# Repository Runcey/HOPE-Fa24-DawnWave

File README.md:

# HOPE-Fa24-DawnWave
## Install the [Espressif plugin](https://github.com/espressif/kicad-libraries) for KiCad!

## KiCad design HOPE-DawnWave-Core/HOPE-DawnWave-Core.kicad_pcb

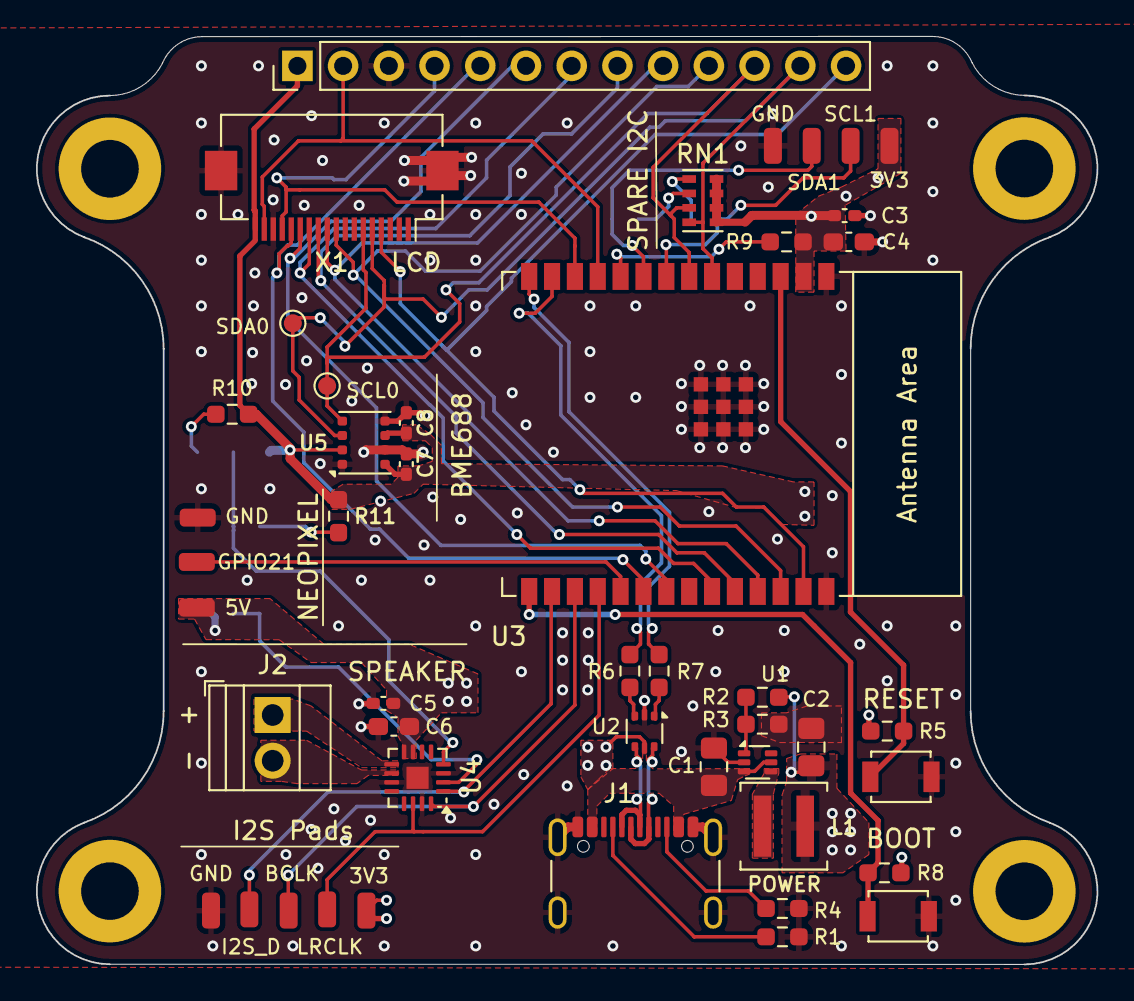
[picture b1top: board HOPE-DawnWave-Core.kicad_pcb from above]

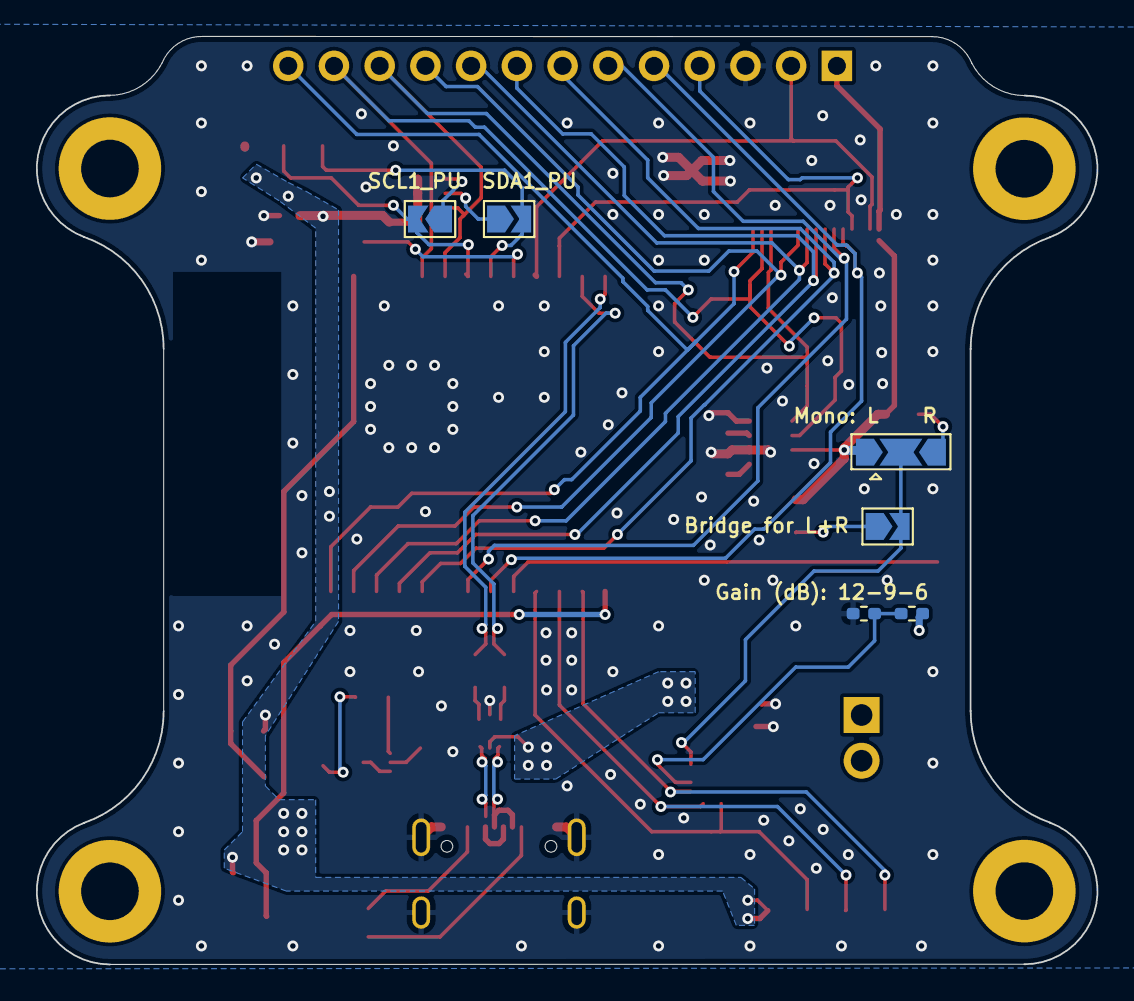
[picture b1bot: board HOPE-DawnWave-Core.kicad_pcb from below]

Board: 2 copper layers, 58.9 x 51.5 mm, 56 parts (6 on the bottom side), 41 nets.

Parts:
C1: 4.7u; C_0805_2012Metric_Pad1.18x1.45mm_HandSolder
C2: 22u; C_0805_2012Metric_Pad1.18x1.45mm_HandSolder
C3, C5: 100n; C_0402_1005Metric_Pad0.74x0.62mm_HandSolder
C4: 22u; C_0603_1608Metric_Pad1.08x0.95mm_HandSolder
C6: 10u; C_0603_1608Metric_Pad1.08x0.95mm_HandSolder
C7, C8: 0.1 µ; C_0402_1005Metric_Pad0.74x0.62mm_HandSolder
H1, H2, H3, H4: MountingHole; MountingHole_3.2mm_M3_ISO7380_Pad
J1: USB_C_Receptacle_USB2.0_16P; USB_C_Receptacle_GCT_USB4105-xx-A_16P_TopMnt_Horizontal
J2: Screw_Terminal_01x02; TerminalBlock_Xinya_XY308-2.54-2P_1x02_P2.54mm_Horizontal
J3: Conn_01x13_Pin; PinHeader_1x13_P2.54mm_Vertical
JP1, JP2: PU; SolderJumper-2_P1.3mm_Open_TrianglePad1.0x1.5mm
JP3: LR_SEL; SolderJumper-3_P2.0mm_Open_TrianglePad1.0x1.5mm
JP5: MONO_SEL; SolderJumper-2_P1.3mm_Open_TrianglePad1.0x1.5mm
L1: 1uH; L_Coilcraft_XAL4020-XXX
R1, R4: 5.1k; R_0603_1608Metric_Pad0.98x0.95mm_HandSolder
R2: 453k; R_0603_1608Metric_Pad0.98x0.95mm_HandSolder
R3: 100k; R_0603_1608Metric_Pad0.98x0.95mm_HandSolder
R5, R8, R9: 10k; R_0603_1608Metric_Pad0.98x0.95mm_HandSolder
R6, R7: 0R; R_0603_1608Metric_Pad0.98x0.95mm_HandSolder
R10: 210.2k; R_0603_1608Metric_Pad0.98x0.95mm_HandSolder
R11: 634k; R_0603_1608Metric_Pad0.98x0.95mm_HandSolder
R12, R13: 0R; R_0402_1005Metric_Pad0.72x0.64mm_HandSolder
RN1: 10k; R_Cat16-4
SW1: RST; SW_SPST_B3U-1000P
SW2: BOOT; SW_SPST_B3U-1000P
TP1: +5V; SolderWirePad_1x01_SMD_1x2mm
TP2, TP3: +3.3V; SolderWirePad_1x01_SMD_1x2mm
TP4: SCL1; SolderWirePad_1x01_SMD_1x2mm
TP5: SDA1; SolderWirePad_1x01_SMD_1x2mm
TP6: NP; SolderWirePad_1x01_SMD_1x2mm
TP7: I2S_D; SolderWirePad_1x01_SMD_1x2mm
TP8: BCLK; SolderWirePad_1x01_SMD_1x2mm
TP9: LRCLK; SolderWirePad_1x01_SMD_1x2mm
TP10, TP11, TP12: GND; SolderWirePad_1x01_SMD_1x2mm
TP13: SCL0; TestPoint_Pad_D1.0mm
TP14: SDA0; TestPoint_Pad_D1.0mm
U1: TLV62569DRL; SOT-563
U2: USBLC6-2P6; SOT-666
U3: ESP32-C6-WROOM-1
U4: MAX98357A; TQFN-16-1EP_3x3mm_P0.5mm_EP1.23x1.23mm
U5: BME688; Bosch_LGA-8_3x3mm_P0.8mm_ClockwisePinNumbering
X1: EYE_SPI_DISPLAY_FLIP; Hirose_FH12-18S-0.5SH_1x18-1MP_P0.50mm_Horizontal

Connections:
+3.3V: C2.1, C3.1, C4.1, C7.1, C8.1, J3.1, JP3.1 (A), L1.2, R2.1, R5.1, R8.1, R9.1, R10.2, R11.1, RN1.5 (R4.2), RN1.6 (R3.2), RN1.7 (R2.2), RN1.8 (R1.2), TP2.1, TP3.1, U3.2 (3V3), U5.2 (CSB), U5.6 (VDDIO), U5.8 (VDD), X1.18
/D+: J1.A6 (D+), J1.B6 (D+), U2.6 (I/O1)
/D-: J1.A7 (D-), J1.B7 (D-), U2.4 (I/O2)
/MAX98357A_I2S/Speaker_N: J2.2, U4.10 (OUTN)
/MAX98357A_I2S/Speaker_P: J2.1, U4.9 (OUTP)
/MCU_BOOT: R8.2, SW2.2, U3.15 (GPIO9)
/MCU_EN: R5.2, SW1.2, U3.3 (EN/CHIP_PU)
/MCU_USB_D+: R7.2, U3.14 (GPIO13/USB_D+)
/MCU_USB_D-: R6.2, U3.13 (GPIO12/USB_D-)
/USB_D+: R7.1, U2.1 (I/O1)
/USB_D-: R6.1, U2.3 (I/O2)
GND: C1.1, C2.2, C3.2, C4.2, C5.2, C6.2, C7.2, C8.2, J1.A1 (GND), J1.A12 (GND), J1.B1 (GND), J1.B12 (GND), J1.S1 (SHIELD), J3.3, R1.2, R3.2, R4.2, R13.2, SW1.1, SW2.1, TP10.1, TP11.1, TP12.1, U1.2 (GND), U2.2 (GND), U3.1 (GND), U3.28 (GND), U3.29 (GND), U4.3 (GND), U4.11 (GND), U4.15 (GND), U4.17 (PAD), U5.1 (GND), U5.5 (SDO), U5.7 (GND), X1.16, X1.MP (MountPin)
GPIO_NP: TP6.1, U3.19 (GPIO21)
MCU_BACKLIGHT: J3.2, U3.11 (GPIO10), X1.17
MCU_BCLK: TP8.1, U3.17 (GPIO19), U4.16 (BCLK)
MCU_DISP_SEL: J3.9, U3.25 (U0TXD/GPIO16), X1.10
MCU_DRST: J3.8, U3.24 (U0RXD/GPIO17), X1.11
MCU_D/C: J3.7, U3.23 (GPIO15), X1.12
MCU_I2S_D: TP7.1, U3.16 (GPIO18), U4.1 (DIN)
MCU_LRCLK: TP9.1, U3.18 (GPIO20), U4.14 (LRCLK)
MCU_MISO: J3.6, U3.21 (GPIO23), X1.13
MCU_MOSI: J3.5, U3.20 (GPIO22), X1.14
MCU_SCL0: J3.11, RN1.3 (R3.1), TP13.1, U3.7 (MTDO/GPIO7), U5.4 (SCK), X1.6
MCU_SCL1: JP1.2 (B), TP4.1, U3.8 (GPIO0/ADC1_CH0/XTAL_32K_P)
MCU_SCLK: J3.4, U3.12 (GPIO11), X1.15
MCU_SDA0: J3.12, RN1.4 (R4.1), TP14.1, U3.6 (MTCK/GPIO6/ADC1_CH6), U5.3 (SDI), X1.5
MCU_SDA1: JP2.2 (B), TP5.1, U3.9 (GPIO1/ADC1_CH1/XTAL_32K_N)
MCU_SD_SEL: J3.10, U3.26 (GPIO3/ADC1_CH3), X1.9
MCU_TD: J3.13, U3.27 (GPIO2/ADC1_CH2), X1.4
unnamed: J1.A5 (CC1), R1.1
unnamed: J1.B5 (CC2), R4.1
unnamed: JP1.1 (A), RN1.1 (R1.1)
unnamed: JP2.1 (A), RN1.2 (R2.1)
unnamed: JP3.3 (B), R10.1
unnamed: JP3.2 (C), JP5.2 (B), U4.4 (~SD_MODE)
unnamed: JP5.1 (A), R11.2
unnamed: R2.2, R3.1, U1.1 (FB)
unnamed: L1.1, U1.4 (SW)
unnamed: R9.2, U3.10 (GPIO8)
unnamed: R12.2, R13.1, U4.2 (GAIN_SLOT)
VBUS: C1.2, C5.1, C6.1, J1.A4 (VBUS), J1.A9 (VBUS), J1.B4 (VBUS), J1.B9 (VBUS), R12.1, TP1.1, U1.3 (VIN), U1.5 (EN), U2.5 (VBUS), U4.7 (VDD), U4.8 (VDD)

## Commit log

2024-10-26 initial push for work woa
2024-10-26 removed extra file
2024-10-28 positions of some components - buck converter and usb c - completed
2024-10-28 Moved components to rough areas, not start on connecting
2024-10-28 flipped esp32 to keep 3.3v on right and 5v on left
2024-10-29 fixed gitignore and completed major component placement iteration
2024-10-29 big progress oops
2024-10-29 Initial layout, need to resolve errors
2024-10-30 fixed 2 fixable drc errors - thermal reliefs
2024-10-30 moved vias to fix via in pad stuff
2024-10-31 fixed spacing on high speed lines, added ground via stitching, made power polygons a bit cleaner, silkscreen labeling is still not done but all warnings are gone
2024-11-06 corrected eyespi connector wiring and added a 2.54mm pitch header to break it out in case something bad happens
2024-11-06 a bit better
2024-11-06 functional silkscreen complete
2024-11-07 fab files generated, pcb finalized
2024-11-07 whoa thats a lot of manufacturing files
2024-12-04 messing around with touchscreen stuff
2024-12-12 main and light adjust screen work, need to figure out time implement :,(
2024-12-12 got time working using wifi (pw for wifi redacted tho lol)
